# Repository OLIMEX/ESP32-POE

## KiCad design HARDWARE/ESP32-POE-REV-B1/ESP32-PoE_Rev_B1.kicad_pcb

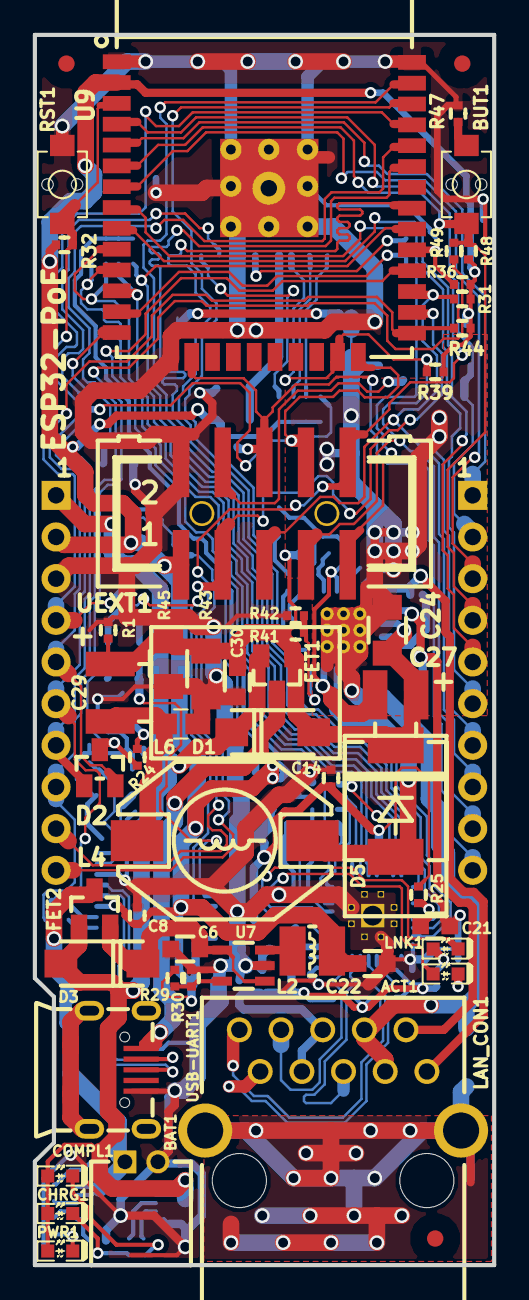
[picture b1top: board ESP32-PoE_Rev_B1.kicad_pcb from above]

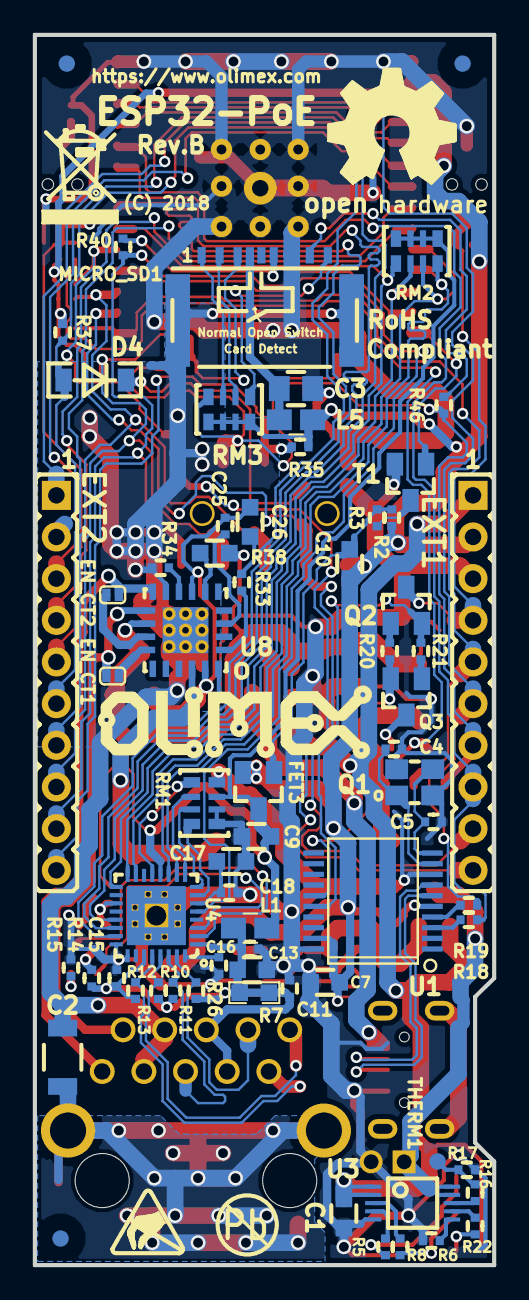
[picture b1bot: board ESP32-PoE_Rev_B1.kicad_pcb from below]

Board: 2 copper layers, 28.0 x 75.0 mm, 119 parts (68 on the bottom side), 100 nets.

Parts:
ACT1: LED/YELLOW/0603; LED_0603_KA
BAT1: DW02R; LIPO_BAT-CON2DW02R
BUT1: IT1185AU2; IT1185AU2_V2
C1, C6, C7, C9, C10, C13, C22, C30: 22uF/6.3V/20%/X5R/C0603; C_0603_5MIL_DWS
C2: 1nF/2000V/10%/X7R/C1206; C_1206_5MIL_DWS_ISO
C3: 47uF/6.3V/20%/X5R/C0805; C_0805_5MIL_DWS
C4, C5: 27pF/50V/5%/C0G/C0402; C_0402_5MIL_DWS
C8, C11, C14, C15, C16, C18, C25: 100nF/16V/10%/X7R/C0402; C_0402_5MIL_DWS
C17: 2.2uF/6.3V/10%/X5R/C0603; C_0603_5MIL_DWS
C21: NA(10uF/6.3V/20%/X5R/C0603); C_0603_5MIL_DWS
C24: 100nF/100V/20%/C1206; C_1206_5MIL_DWS
C26: 1nF/50V/10%/X7R/C0603; C_0603_5MIL_DWS
C27: 15uF/100V/20%/RM2.5/6.3x11mm(Farnell:1281844 ); CPOL-RM2.5mm_6.3x11mm_SMD
C29: 680uF/10V/20%/105C/RM3.5/8x11.5mm; CPOL-RM3.5mm_8.0x11.5mm_SMD
CHRG1: LED/YELLOW/0603; LED_0603_KA
COMPL1: LED/GREEN/0603; LED_0603_KA
D1, D3: 1N5822/SS34/SMA; SMA-KA
D2: BAT54C(SOT23-3); SOT23-3
D4: 1N5819S4(SOD-123); SOD-123_1C-2A_KA
D5: SS510/100V/5A/0.85V/DO214AB(SMC); DO214AB(SMC)_1(K)-2(A)
EN_CT1, EN_CT2: Opened; SJ_1_SMALLER
EXT1, EXT2: NS(HN1x10); HN1x10
FET1, FET2, FET3: WPM2015-3/TR; SOT23
FID1, FID2, FID3, FID4, FID5, FID6: Fiducial; Fiducial1x3
L1, L5, L6: FB0805/600R/2A; L_0805_5MIL_DWS
L2: 2.2uH/1.5A/DCR<0.1R/CD32; CD32
L4: 33uH/2.1A/DCR=0.1R/20%/DBS135(PD3316MT330); DBS135
LAN_CON1: RJP-003TC1(LPJ4112CNL)
LNK1: LED/GREEN/0603; LED_0603_KA
MICRO_SD1: TFC-9P-1.7H(ATFFS150A01BR016); uSD(TFC-9P-1.xH(ATFFS150A01BR016))
PWR1: LED/RED/0603; LED_0603_KA
Q1: Q12MHz/20pF/10ppm/4P/3.2x2.5mm; TSX-3.2x2.5mm_GND(3)
Q2, Q3: BC817-40(SOT23); SOT23
R1, R2, R17, R25, R36, R37, R39, R48: 10k/R0402; R_0402_5MIL_DWS
R3, R16, R20, R21, R32: 1k/R0402; R_0402_5MIL_DWS
R5, R6, R8, R14, R15, R22, R31, R35: 2.2k/R0402; R_0402_5MIL_DWS
R7: 0R(board_mounted); 0R_0603
R10, R11, R12, R13, R34: 49.9R/1%/R0402; R_0402_5MIL_DWS
R18, R19, R24, R46, R47: 220R/R0402; R_0402_5MIL_DWS
R26: 12.1k/1%/R0402; R_0402_5MIL_DWS
R29: 4.99k/1%/R0402; R_0402_5MIL_DWS
R30: 1.1k/1%/R0402; R_0402_5MIL_DWS
R33: 47k/R0402; R_0402_5MIL_DWS
R38: 25.5k/1%/R0603; R_0603_5MIL_DWS
R40: 10R/R0402; R_0402_5MIL_DWS
R41: 1k/1%/R0402; R_0402_5MIL_DWS
R42: 3.01k/1%/R0402; R_0402_5MIL_DWS
R43, R45: 220R/5%/0.25W/R1206; R_1206_5MIL_DWS
R44, R49: NA/R0402; R_0402_5MIL_DWS
RM1, RM2, RM3: RA1206_(4X0603)_4B8_2.2k; R_MATRIX_4
RST1: IT1185AU2; IT1185AU2_V2
Ref**: Val**; LOGO_ANTISTATIC_SMALL_4.5mmX2.8mm
T1: DTC114YKA(SOT-23); SOT23
THERM1: TESTPAD; TESTPAD_40-ROUND
U1: CH340T(SSOP20W); SSOP-20W
U3: MCP73833(MSOP10); MSOP-10_Pitch-0.5mm_3.00x3.00x1.00mm
U4: LAN8710A-EZC(QFN32); QFN32_EP(33)_5.00x5.00x0.90mm_Pitch_0.50mm
U7: SY8089AAAC(SOT23-5); SOT-23-5
U8: Si3402-B-GM(QFN-20_5x5mm); QFN-20_5x5mm(Si3402-B-GM)
U9: ESP-WROOM-32; ESP-WROOM-32_MODULE
UEXT1: B-V-10-LF(GBH254SMT-10); GBH-254-SMT-10
USB-UART1: MISB-SWMM-5B-LF(USB_MICRO); USB-MICRO_MISB-SWMM-5B_LF

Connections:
+3.3VLAN: C9.1, C14.1, FET3.3, L1.1, R25.2, RM1.3.1, RM2.1.1, RM2.2.1, RM2.3.1, RM2.4.1, U4.12
+3V3: C7.1, C8.1, C10.1, C22.1, EXT1.2, FET3.2, L2.2, L5.1, R2.1, R29.2, R31.1, R32.1, R35.1, R36.1, R37.1, R39.1, R44.2, R48.1, RM3.1.2, RM3.2.2, RM3.3.2, RM3.4.2, U1.5, U1.19, U9.2, UEXT1.1
+5V: C1.1, CHRG1.2, COMPL1.2, D1.1, D3.2, EXT1.1, FET1.2, FET2.1, PWR1.2, U3.1, U3.2
+5VP: C24.1, C27.1, C29.1, C30.1, D1.2, D5.1, FET1.1, R1.1, R38.2, R41.1, R43.1, R45.1, U8.12
/#PG(#TE): R22.2, U3.7
/+5V_USB: FET1.3, USB-UART1.1
/D_Com: D2.3, R24.2, R49.2
/ESP_EN: EXT1.4, Q2.3, R32.2, RST1.1, U9.3
/GPI34/BUT1: BUT1.1, EXT2.4, R48.2, R49.1, U9.6
/GPI35: EXT2.3, U9.7
/GPI36/U1RXD: D4.2, EXT2.2, R37.2, U9.4
/GPI39: EXT2.1, U9.5
/GPIO0: D2.2, EXT1.5, R44.1, U9.25
/GPIO1/U0TXD: EXT1.6, R19.2, U9.35
/GPIO2/HS2_DATA0: D2.1, EXT1.7, R46.1, RM3.4.1, U9.24, UEXT1.8
/GPIO3/U0RXD: EXT1.8, R18.2, U9.34
/GPIO4/U1TXD: EXT1.9, U9.26, UEXT1.3
/GPIO5/SPI_CS: EXT1.10, R36.2, U9.29, UEXT1.10
/GPIO12/PHY_PWR: T1.1, U9.14
/GPIO13/I2C-SDA: EXT2.10, R35.2, U9.16, UEXT1.6
/GPIO14/HS2_CLK: EXT2.9, R40.1, U9.13, UEXT1.9
/GPIO15/HS2_CMD: EXT2.8, MICRO_SD1.3, R39.2, U9.23, UEXT1.7
/GPIO16/I2C-SCL: EXT2.7, R31.2, U9.27, UEXT1.5
/GPIO17/EMAC_CLK_OUT_180: U4.5, U9.28
/GPIO18/MDIO(RMII): RM2.4.2, U4.16, U9.30
/GPIO19/EMAC_TXD0(RMII): U4.22, U9.31
/GPIO21/EMAC_TX_EN(RMII): U4.21, U9.33
/GPIO22/EMAC_TXD1(RMII): U4.23, U9.36
/GPIO23/MDC(RMII): U4.17, U9.37
/GPIO25/EMAC_RXD0(RMII): RM2.2.2, U4.11, U9.10
/GPIO26/EMAC_RXD1(RMII): RM2.1.2, U4.10, U9.11
/GPIO27/EMAC_RX_CRS_DV: RM2.3.2, U4.15, U9.12
/GPIO32: EXT2.6, U9.8
/GPIO33: EXT2.5, U9.9
/STAT1: R8.2, U3.3
/STAT2: R5.2, U3.4
Earth: C2.1, C24.2, LAN_CON1.7, LAN_CON1.8, MICRO_SD1.CH1, R34.1, U8.9, U8.21
GND: BAT1.2, C1.2, C3.2, C4.2, C5.2, C6.2, C7.2, C8.2, C9.2, C11.2, C13.2, C14.2, C15.2, C16.2, C17.2, C18.2, C21.1, C22.2, C30.2, EXT1.3, L6.2, MICRO_SD1.6, Q1.3, R1.2, R6.2, R15.2, R17.2, R26.2, R30.2, R42.2, R43.2, R45.2, R47.2, RM1.1.1, RM1.2.1, RM1.4.1, RST1.2, T1.2, U1.8, U1.20, U3.5, U4.24, U4.25, U4.33, U7.2, U9.1, U9.15, U9.38, U9.39, UEXT1.2, USB-UART1.5
unnamed: ACT1.1, R15.1
unnamed: ACT1.2, U4.3
unnamed: BAT1.1, FET2.3, U3.9, U3.10
unnamed: BUT1.2, R47.1
unnamed: C2.2, LAN_CON1.0
unnamed: C3.1, L5.2, MICRO_SD1.4
unnamed: C4.1, Q1.1, U1.9
unnamed: C5.1, Q1.2, U1.10
unnamed: C6.1, D3.1, FET2.2, U7.1, U7.4
unnamed: C10.2, FET3.1, R2.2, R3.1
unnamed: C11.1, LAN_CON1.4, LAN_CON1.5, R7.2
unnamed: C13.1, C15.1, C16.1, L1.2, R7.1, R10.1, R11.1, R12.1, R13.1, R14.1, U4.1, U4.27
unnamed: C17.1, C18.1, U4.6
unnamed: C21.2, R25.1, U4.19
unnamed: C25.1, U8.3
unnamed: C25.2, C26.2, C27.2, U8.7, U8.19
unnamed: C26.1, R33.1
unnamed: C29.2, L4.2, L6.1
unnamed: CHRG1.1, R8.1
unnamed: COMPL1.1, R5.1
unnamed: D4.1, UEXT1.4
unnamed: D5.2, L4.1, U8.18
unnamed: EN_CT1.1, U8.14
unnamed: EN_CT2.1, U8.13
unnamed: L2.1, U7.3
unnamed: LAN_CON1.1, R13.2, U4.29
unnamed: LAN_CON1.2, R12.2, U4.28
unnamed: LAN_CON1.3, R11.2, U4.31
unnamed: LAN_CON1.6, R10.2, U4.30
unnamed: LNK1.1, U4.2
unnamed: LNK1.2, R14.2
unnamed: MICRO_SD1.1, RM3.3.1
unnamed: MICRO_SD1.2, RM3.2.1
unnamed: MICRO_SD1.5, R40.2
unnamed: MICRO_SD1.7, R46.2
unnamed: MICRO_SD1.8, RM3.1.1
unnamed: PWR1.1, R22.1
unnamed: Q2.1, R20.2
unnamed: Q2.2, R21.1, U1.16
unnamed: Q3.1, R21.2
unnamed: Q3.2, R20.1, U1.15
unnamed: Q3.3, R24.1
unnamed: R3.2, T1.3
unnamed: R6.1, U3.6
unnamed: R16.1, U3.8
unnamed: R16.2, R17.1, THERM1.1
unnamed: R18.1, U1.3
unnamed: R19.1, U1.4
unnamed: R26.1, U4.32
unnamed: R29.1, R30.1, U7.5
unnamed: R33.2, U8.1
unnamed: R34.2, U8.8
unnamed: R38.1, U8.6
unnamed: R41.2, R42.1, U8.20
unnamed: RM1.1.2, U4.7
unnamed: RM1.2.2, U4.8
unnamed: RM1.3.2, U4.9
unnamed: RM1.4.2, U4.13
unnamed: U1.6, USB-UART1.3
unnamed: U1.7, USB-UART1.2
Spare1: EN_CT1.2, LAN_CON1.9, U8.11
Spare2: EN_CT2.2, LAN_CON1.10, U8.10

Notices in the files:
HARDWARE/ESP32-POE-REV-B1/ESP32-PoE_Rev_B1.kicad_pcb:
(C) 2018
